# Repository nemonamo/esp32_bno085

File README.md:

<h1 align="center">ESP32 BNO085</h1>

<p align="center">
  <strong>9축 모션 센싱을 위한 ESP32-S3 + BNO085 KiCad 하드웨어 설계.</strong>
</p>

<p align="center">
  <a href="#주요-특징">주요 특징</a> |
  <a href="#저장소-구성">구성</a> |
  <a href="#프로젝트-열기">열기</a> |
  <a href="#제작-체크리스트">제작</a> |
  <a href="#라이선스">라이선스</a>
</p>

<p align="center">
  한국어 |
  <a href="docs/i18n/README.en.md">English</a> |
  <a href="docs/i18n/README.zh-CN.md">中文</a> |
  <a href="docs/i18n/README.ja.md">日本語</a>
</p>

이 저장소는 BNO085 9축 스마트 IMU를 중심으로 한 소형 ESP32-S3 보드의 KiCad 설계 파일을 담고 있습니다. 회로도, PCB 레이아웃, 로컬 풋프린트 라이브러리, fabrication-toolkit 설정은 버전 관리하고, 생성된 Gerber와 분석 결과는 Git에 포함하지 않습니다.

## 주요 특징

- **ESP32-S3 모듈** - Wi-Fi/BLE가 가능한 MCU 모듈 풋프린트.
- **BNO085 스마트 IMU** - 가속도계, 자이로, 자력계, 센서 퓨전용 9축 센서.
- **USB-C 인터페이스** - USB 2.0 Type-C 리셉터클 기반 연결.
- **로컬 풋프린트 포함** - BNO085와 Molex 커넥터 풋프린트를 저장소에 포함.
- **제작 설정 버전 관리** - 반복 가능한 제조 파일 생성을 위한 fabrication-toolkit 설정 포함.

## 저장소 구성

```text
esp32_bno085.kicad_pro          KiCad 프로젝트 파일
esp32_bno085.kicad_sch          회로도
esp32_bno085.kicad_pcb          PCB 레이아웃
fp-lib-table                    로컬 풋프린트 라이브러리 테이블
BNO085.pretty/                  BNO085 풋프린트
530480210.pretty/               Molex 커넥터 풋프린트
fabrication-toolkit-options.json
```

생성 파일은 제외합니다.

```text
analysis/
production/
*-backups/
.history/
*.kicad_prl
```

## 프로젝트 열기

1. KiCad 8 이상을 설치합니다.
2. 저장소를 clone합니다.
3. KiCad에서 `esp32_bno085.kicad_pro`를 엽니다.
4. `fp-lib-table` 기준으로 로컬 풋프린트가 정상 연결되는지 확인합니다.
5. 제조 파일을 내보내기 전에 ERC와 DRC를 실행합니다.

```powershell
git clone https://github.com/nemonamo/esp32_bno085.git
cd esp32_bno085
```

## 제작 체크리스트

PCB 주문 전 확인할 항목:

- `esp32_bno085.kicad_sch`에서 KiCad ERC 실행
- `esp32_bno085.kicad_pcb`에서 KiCad DRC 실행
- 현재 보드 기준으로 Gerber, drill, BOM, CPL 재내보내기
- USB D+/D- clearance와 커넥터 방향 확인
- BNO085 I2C pull-up과 전원 레일 확인
- 제작 업체의 설계 규칙이 현재 PCB 제약과 맞는지 확인

이전 보드 리뷰에서는 JLCPCB 관련 copper geometry, 작은 via, USB D- clearance, silkscreen/text warning, BNO085 environmental I2C pull-up을 중점적으로 확인했습니다. 레이아웃을 바꿀 때마다 검사를 다시 실행하세요.

## 이 저장소가 아닌 것

- 펌웨어는 포함하지 않습니다.
- 생성된 production package는 포함하지 않습니다.
- 최신 커밋이 그대로 제작 검증을 마쳤다고 보장하지 않습니다.

## 보안과 안전

하드웨어 저장소도 제작 압축 파일, 공급업체 export, 주문 파일, 스크린샷, 로컬 메모를 통해 개인 정보나 프로젝트 정보를 노출할 수 있습니다. production export와 분석 보고서는 검토 전까지 로컬에만 보관하세요.

## 라이선스

현재 오픈소스 하드웨어/소프트웨어 라이선스가 선언되어 있지 않습니다. 외부 재사용, 제작, 기여를 받기 전에 `LICENSE` 파일을 추가하세요.

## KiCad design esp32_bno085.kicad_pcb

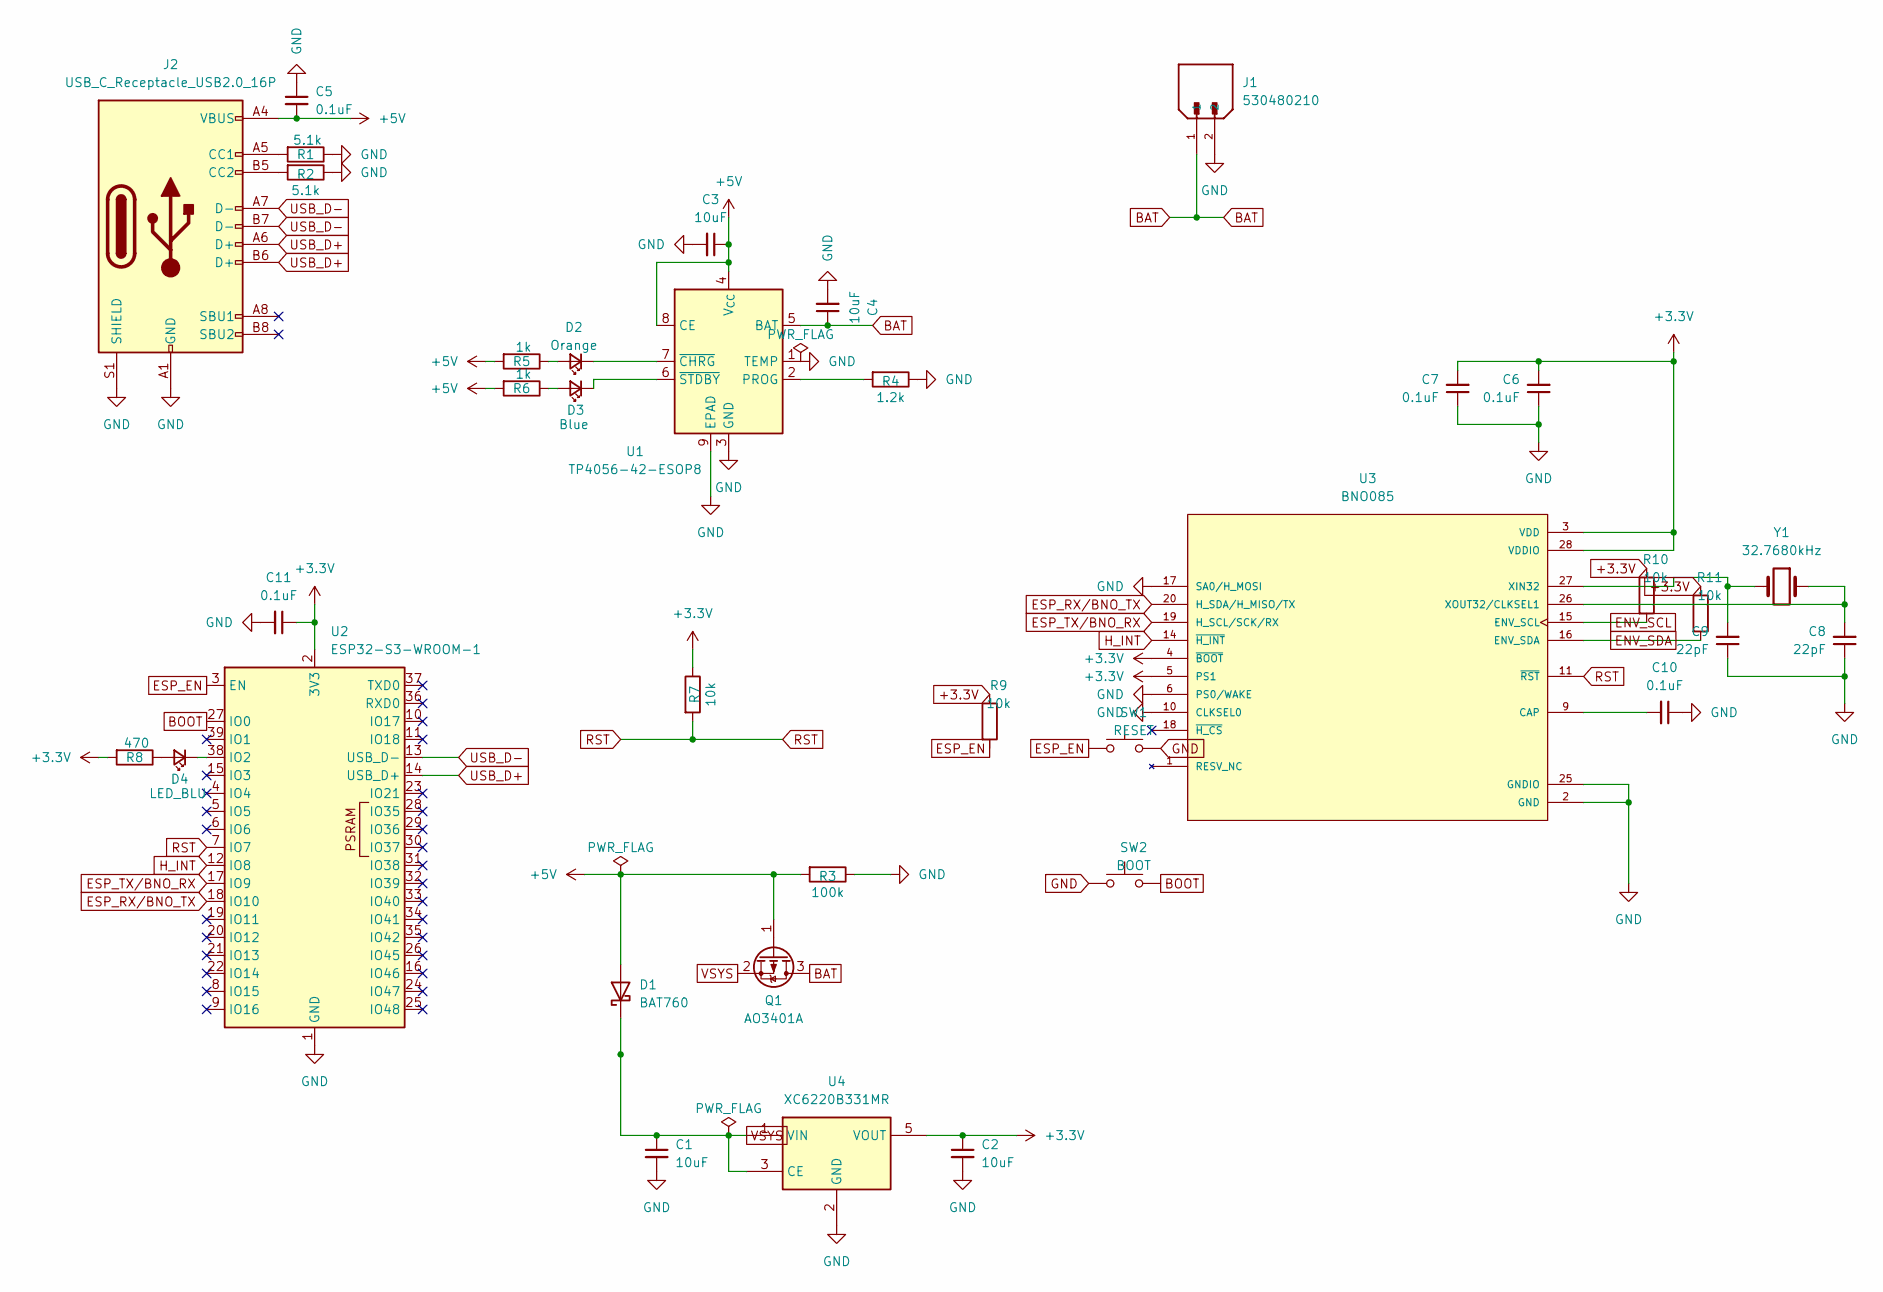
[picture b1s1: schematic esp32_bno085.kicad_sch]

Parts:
C1, C2, C3, C4: 10uF; C_0402_1005Metric_Pad0.74x0.62mm_HandSolder
C5, C6, C7, C10, C11: 0.1uF; C_0402_1005Metric_Pad0.74x0.62mm_HandSolder
C8, C9: 22pF; C_0402_1005Metric_Pad0.74x0.62mm_HandSolder
D1: BAT760; D_SOD-323; MPN BAT760-7; LCSC C124187
D2: Orange; LED_0603_1608Metric_Pad1.05x0.95mm_HandSolder
D3: Blue; LED_0603_1608Metric_Pad1.05x0.95mm_HandSolder
D4: LED_BLU; LED_0603_1608Metric_Pad1.05x0.95mm_HandSolder
J1: 530480210; MOLEX_530480210; PARTREV A; LCSC C505099
J2: USB_C_Receptacle_USB2.0_16P; USB_C_Receptacle_HRO_TYPE-C-31-M-12; MPN TYPE-C-31-M-12; LCSC C165948
Q1: AO3401A; SOT-23; MPN AO3401A; LCSC C15127
R1, R2: 5.1k; R_0402_1005Metric_Pad0.72x0.64mm_HandSolder
R3: 100k; R_0402_1005Metric_Pad0.72x0.64mm_HandSolder
R4: 1.2k; R_0402_1005Metric_Pad0.72x0.64mm_HandSolder
R5, R6: 1k; R_0402_1005Metric_Pad0.72x0.64mm_HandSolder
R7, R9, R10, R11: 10k; R_0402_1005Metric_Pad0.72x0.64mm_HandSolder
R8: 470; R_0402_1005Metric_Pad0.72x0.64mm_HandSolder
SW1: RESET; SW_SPST_B3U-1000P
SW2: BOOT; SW_SPST_B3U-1000P
U1: TP4056-42-ESOP8; SOIC-8-1EP_3.9x4.9mm_P1.27mm_EP2.41x3.3mm_ThermalVias; MPN TP4056-42-ESOP8; LCSC C16581
U2: ESP32-S3-WROOM-1
U3: BNO085; IC_BNO085; PARTREV v1.17; LCSC C5189642
U4: XC6220B331MR; SOT-23-5; MPN XC6220B331MR-G; LCSC C86534
Y1: 32.7680kHz; Crystal_SMD_3215-2Pin_3.2x1.5mm

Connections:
+3.3V: C2.1, C6.2, C7.2, C11.1, R7.1, R8.2, R9.1, R10.1, R11.1, U2.2 (3V3), U3.3 (VDD), U3.4 (~BOOT), U3.5 (PS1), U3.28 (VDDIO), U4.5 (VOUT)
+5V: C3.1, C5.2, D1.2 (A), J2.A4 (VBUS), J2.A9 (VBUS), J2.B4 (VBUS), J2.B9 (VBUS), Q1.1 (G), R3.2, R5.2, R6.2, U1.4 (V_{CC}), U1.8 (CE)
BAT: C4.1, J1.1, Q1.3 (D), U1.5 (BAT)
BOOT: SW2.2, U2.27 (IO0)
ENV_SCL: R10.2, U3.15 (ENV_SCL)
ENV_SDA: R11.2, U3.16 (ENV_SDA)
ESP_EN: R9.2, SW1.1, U2.3 (EN)
ESP_RX/BNO_TX: U2.18 (IO10), U3.20 (H_SDA/H_MISO/TX)
ESP_TX/BNO_RX: U2.17 (IO9), U3.19 (H_SCL/SCK/RX)
GND: C1.2, C2.2, C3.2, C4.2, C5.1, C6.1, C7.1, C8.1, C9.1, C10.1, C11.2, J1.2, J2.A1 (GND), J2.A12 (GND), J2.B1 (GND), J2.B12 (GND), J2.S1 (SHIELD), R1.1, R2.1, R3.1, R4.1, SW1.2, SW2.1, U1.1 (TEMP), U1.3 (GND), U1.9 (EPAD), U2.1 (GND), U2.40 (GND), U2.41 (GND), U3.2 (GND), U3.6 (PS0/WAKE), U3.10 (CLKSEL0), U3.17 (SA0/H_MOSI), U3.25 (GNDIO), U4.2 (GND)
H_INT: U2.12 (IO8), U3.14 (~H_INT)
unnamed: D2.2 (A), R5.1
unnamed: D2.1 (K), U1.7 (~CHRG)
unnamed: D3.2 (A), R6.1
unnamed: D3.1 (K), U1.6 (~STDBY)
unnamed: D4.2 (A), R8.1
unnamed: D4.1 (K), U2.38 (IO2)
unnamed: J2.A5 (CC1), R1.2
unnamed: J2.B5 (CC2), R2.2
unnamed: R4.2, U1.2 (PROG)
unnamed: C10.2, U3.9 (CAP)
unnamed: C9.2, U3.27 (XIN32), Y1.2
unnamed: C8.2, U3.26 (XOUT32/CLKSEL1), Y1.1
RST: R7.2, U2.7 (IO7), U3.11 (~RST)
USB_D+: J2.A6 (D+), J2.B6 (D+), U2.14 (USB_D+)
USB_D-: J2.A7 (D-), J2.B7 (D-), U2.13 (USB_D-)
VSYS: C1.1, D1.1 (K), Q1.2 (S), U4.1 (VIN), U4.3 (CE)

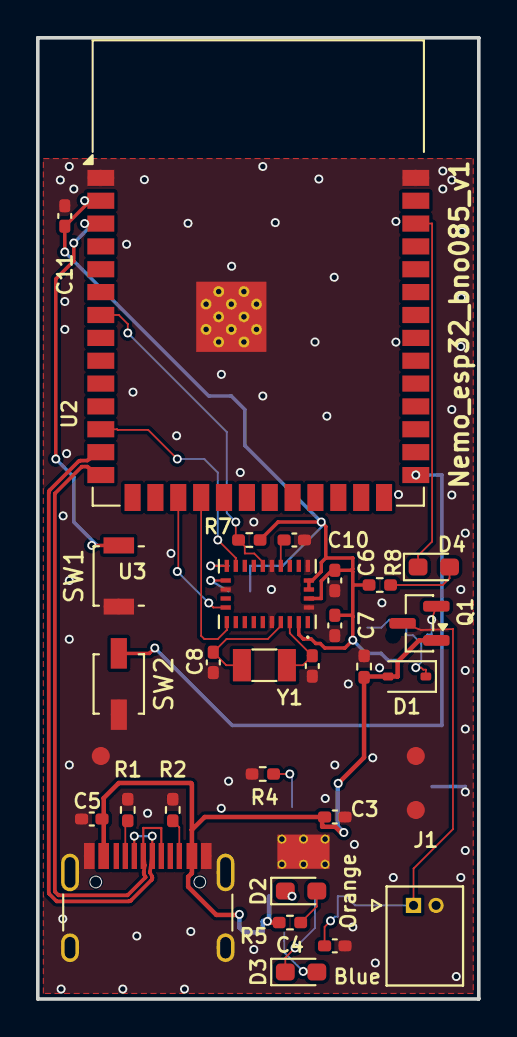
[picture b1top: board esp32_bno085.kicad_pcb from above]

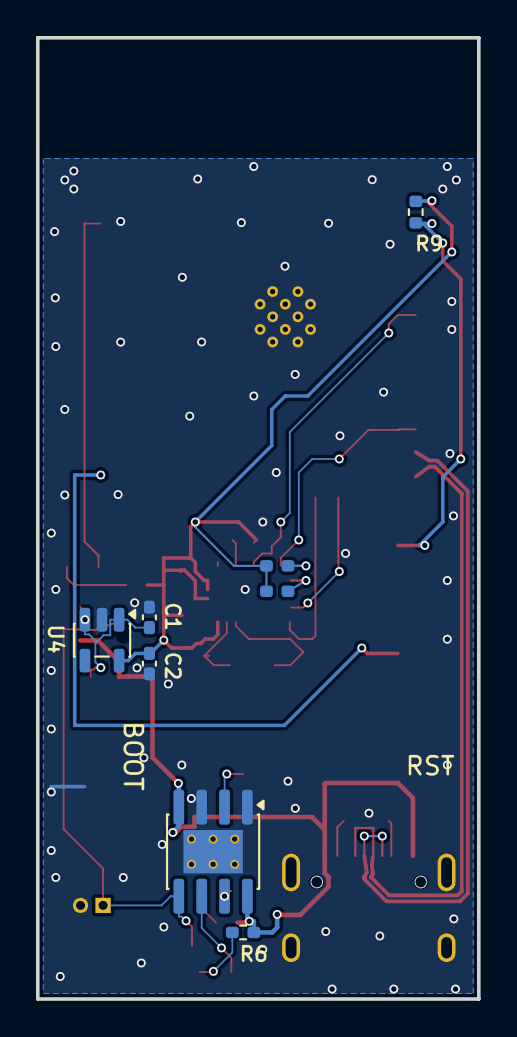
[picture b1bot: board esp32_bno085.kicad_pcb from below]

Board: 2 copper layers, 24.5 x 53.4 mm, 39 parts (8 on the bottom side), 27 nets.

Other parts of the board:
FID1, FID2, FID3: Fiducial_1mm_Mask2mm

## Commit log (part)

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2026-06-26 Initial KiCad project
2026-06-26 Clean KiCad DRC warnings

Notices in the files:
README.md:
License: not declared
